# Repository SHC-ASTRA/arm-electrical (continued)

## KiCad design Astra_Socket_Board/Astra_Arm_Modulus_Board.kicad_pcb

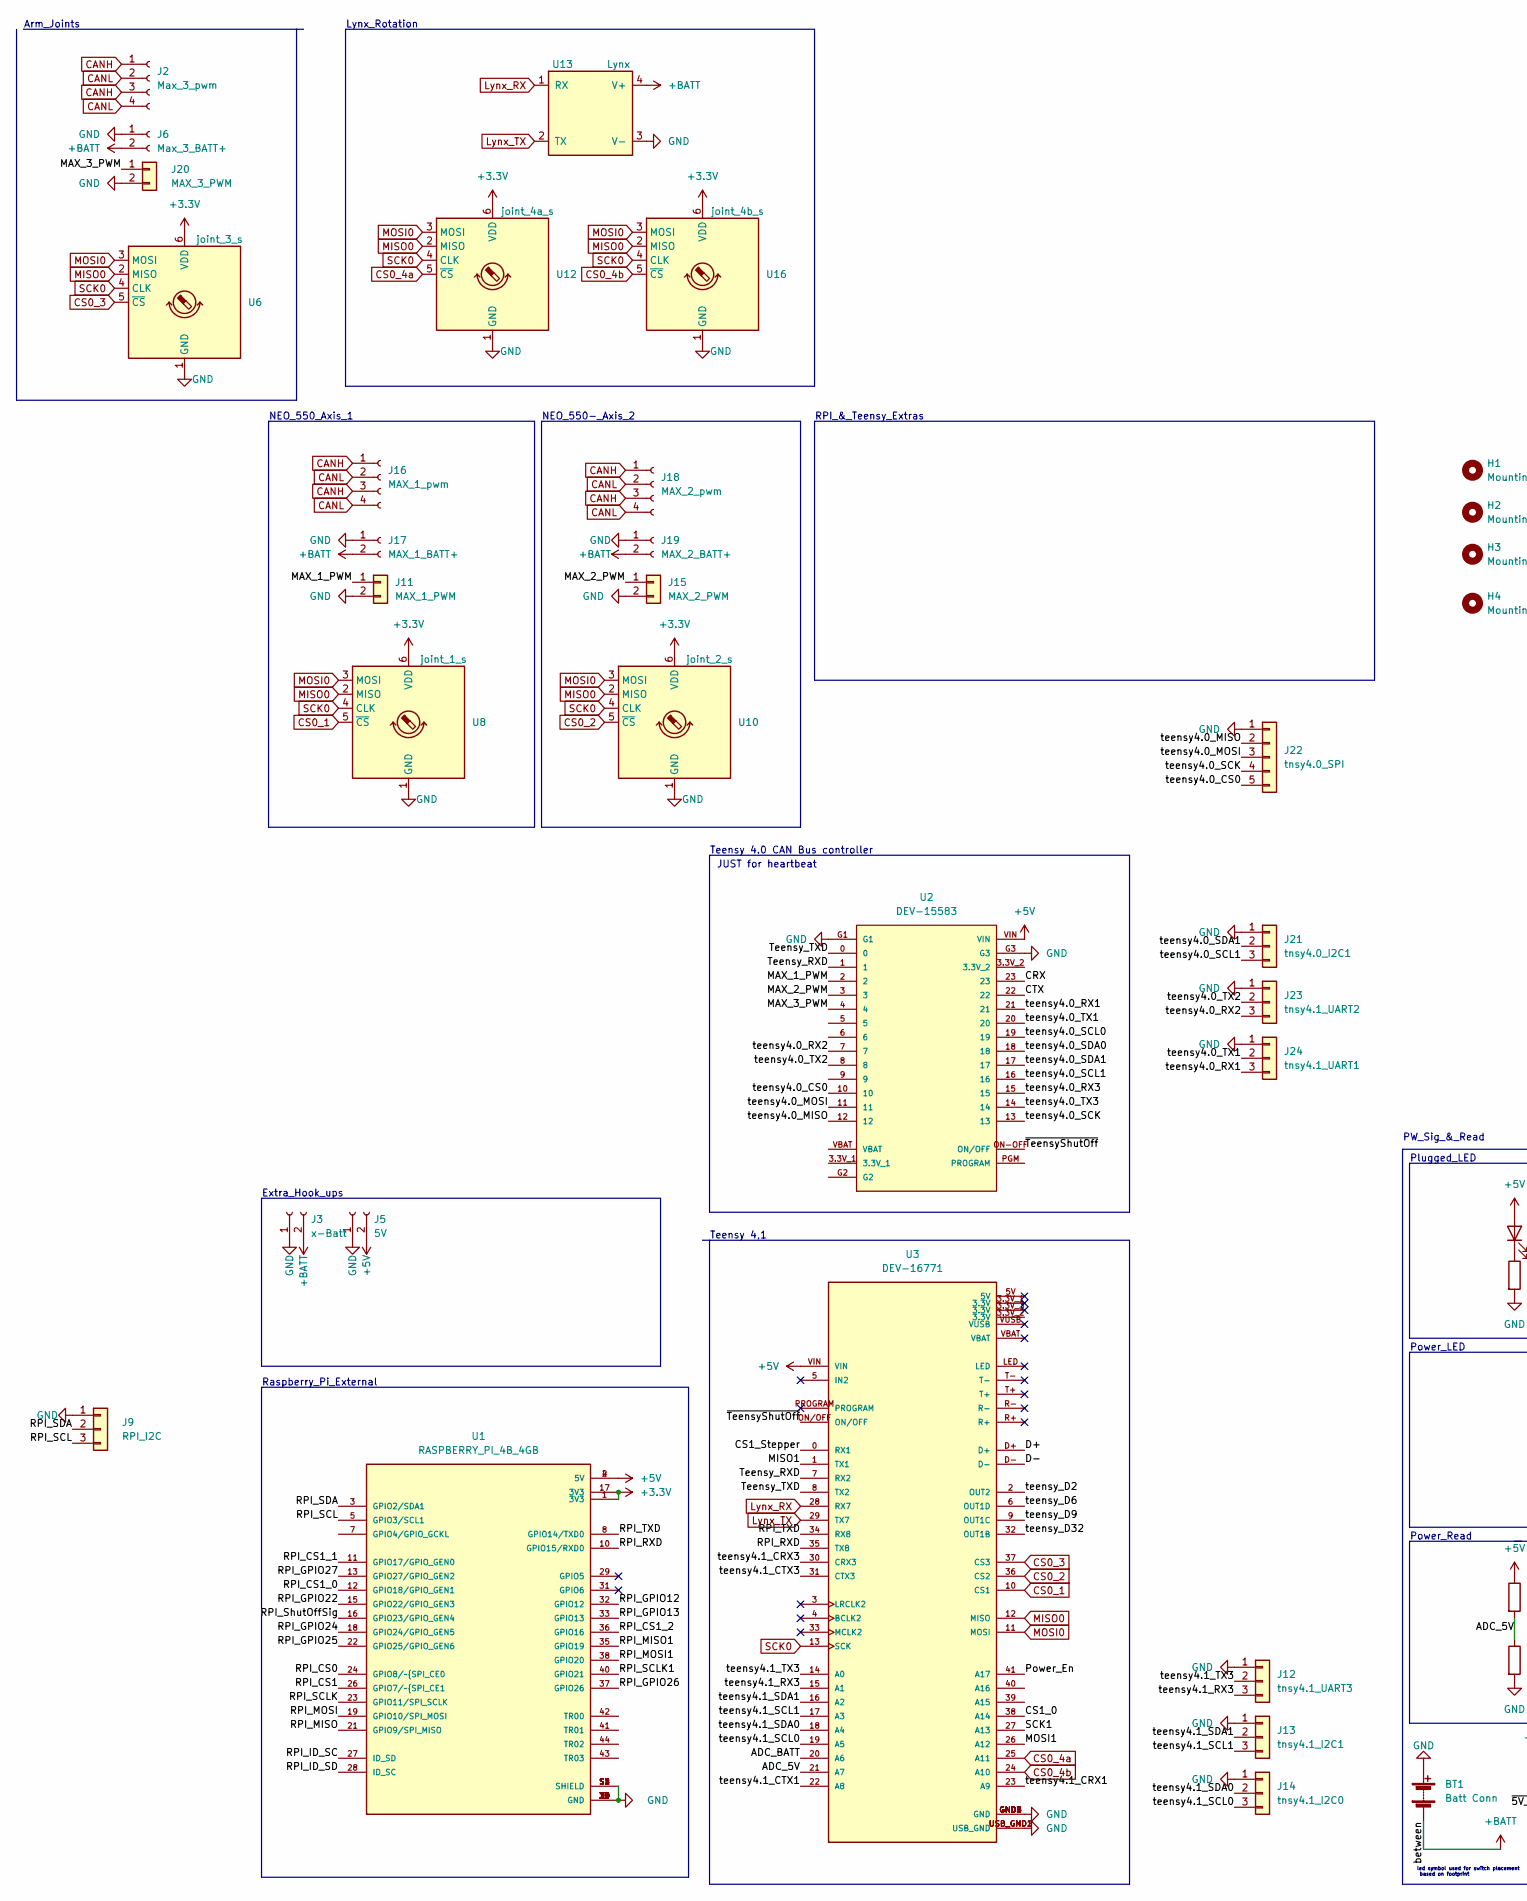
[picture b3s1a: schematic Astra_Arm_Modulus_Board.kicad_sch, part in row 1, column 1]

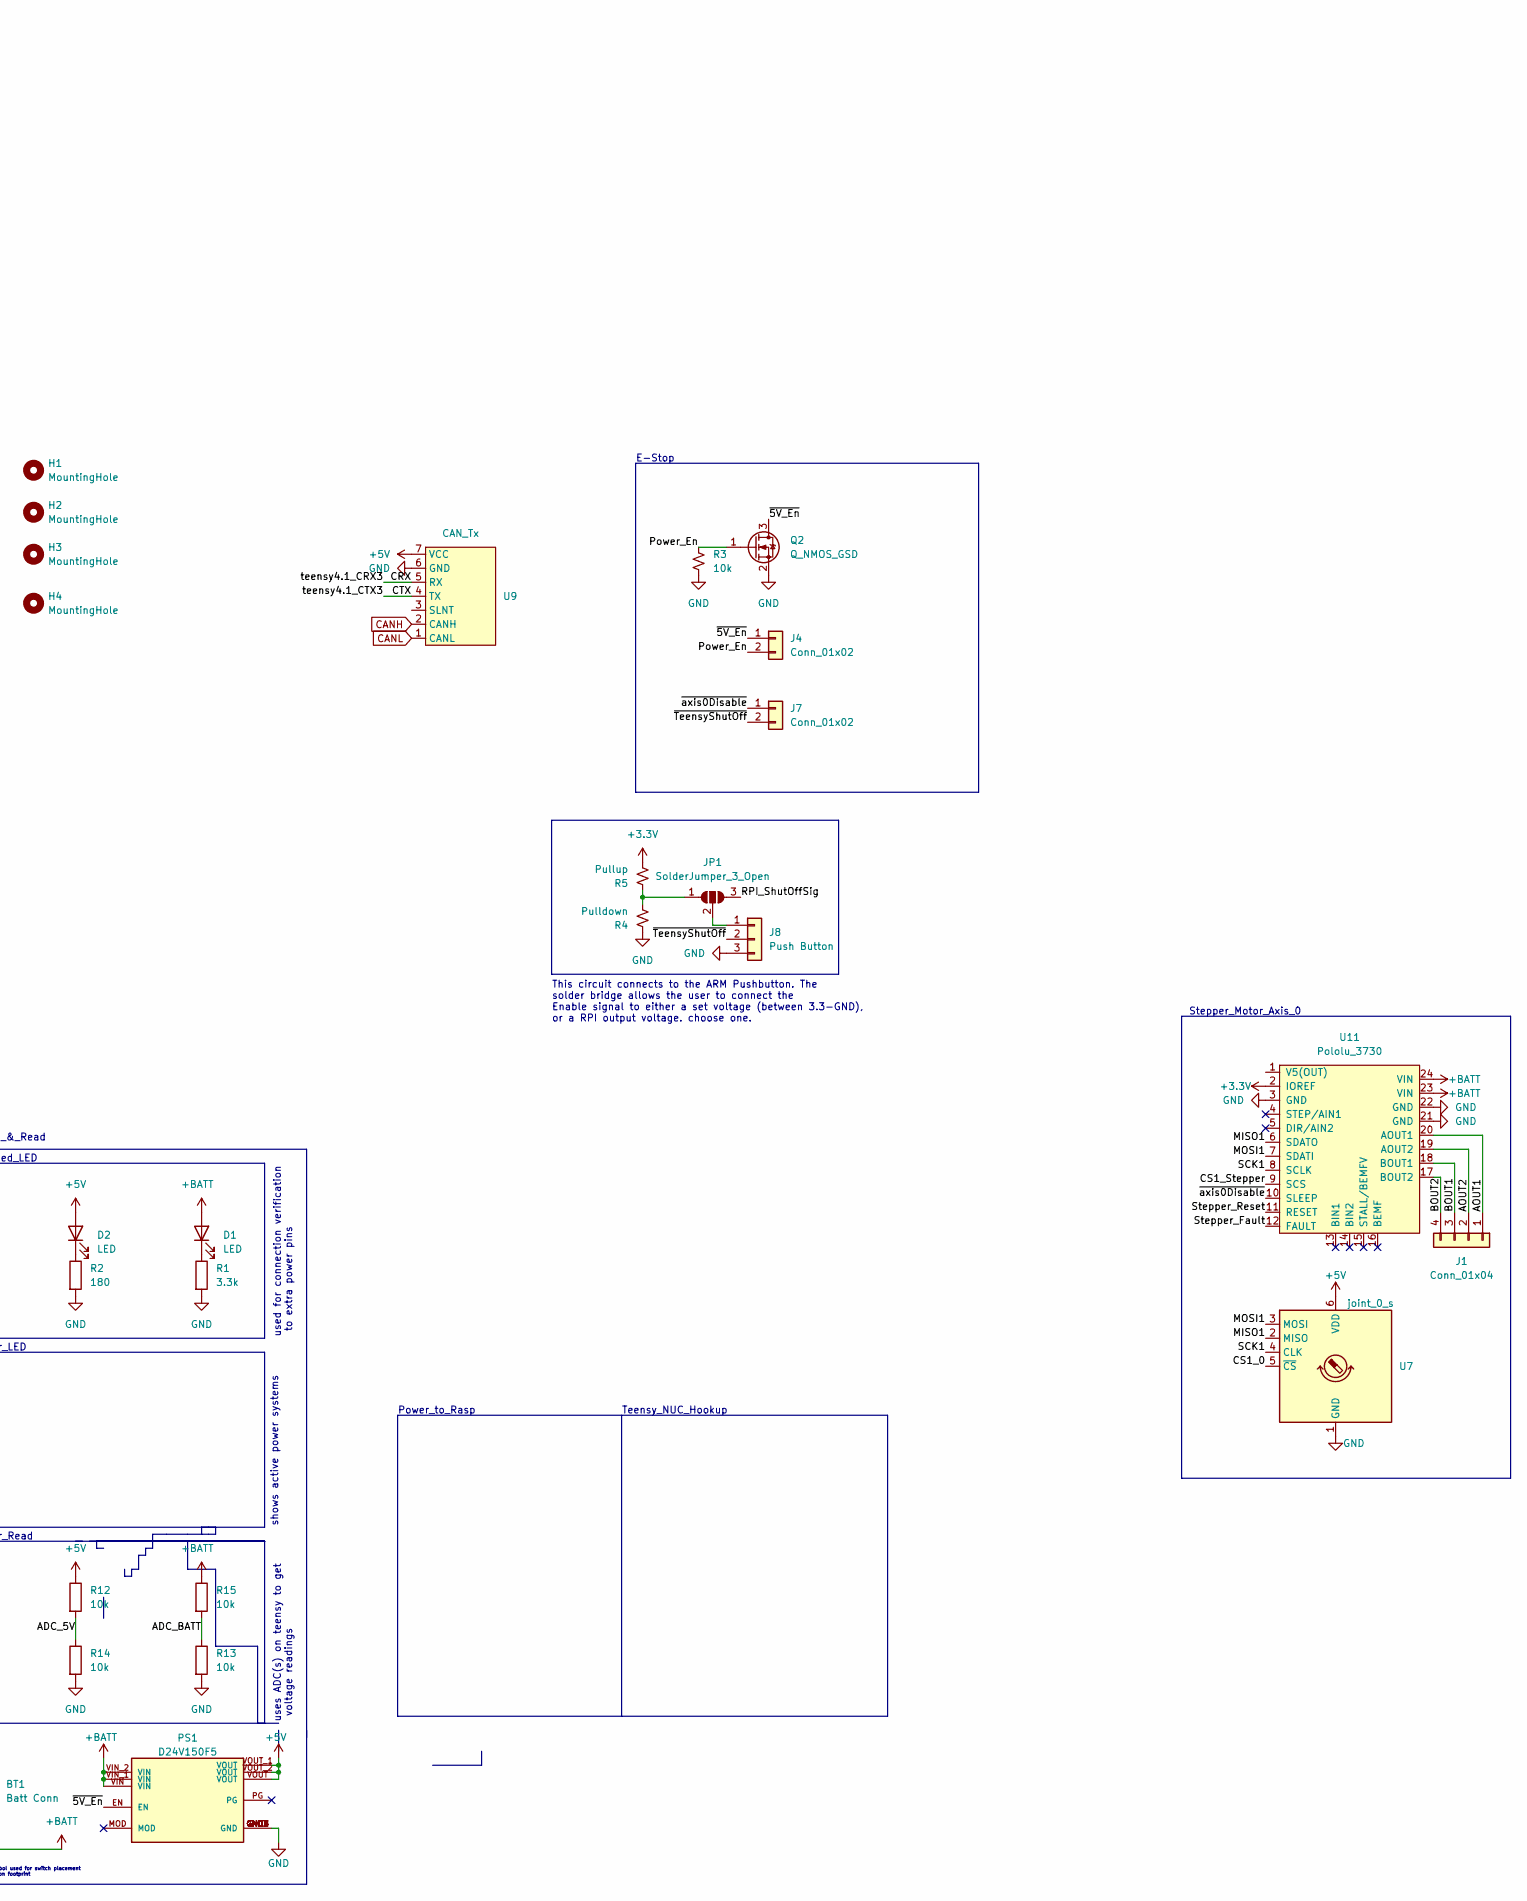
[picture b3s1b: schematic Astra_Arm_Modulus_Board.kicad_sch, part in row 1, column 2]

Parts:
BT1: Batt Conn; AMASS_XT60-F_1x02_P7.20mm_Vertical
D1, D2: LED; LED_0603_1608Metric_Pad1.05x0.95mm_HandSolder
H1, H2, H3, H4: MountingHole; MountingHole_3mm
J1: Conn_01x04; JST_XH_S4B-XH-A_1x04_P2.50mm_Horizontal
J2: Max_3_pwm; JST_EH_B4B-EH-A_1x04_P2.50mm_Vertical
J3: x-Batt; AMASS_XT60-F_1x02_P7.20mm_Vertical
J4, J7: Conn_01x02; PinSocket_1x02_P2.54mm_Vertical
J5: 5V; AMASS_XT60-F_1x02_P7.20mm_Vertical
J6: Max_3_BATT+; AMASS_XT60-F_1x02_P7.20mm_Vertical
J8: Push Button; JST_PH_B3B-PH-K_1x03_P2.00mm_Vertical
J9: RPI_I2C; PinHeader_1x03_P2.54mm_Vertical
J11: MAX_1_PWM; JST_PH_B2B-PH-K_1x02_P2.00mm_Vertical
J12: tnsy4.1_UART3; PinHeader_1x03_P2.54mm_Vertical
J13: tnsy4.1_I2C1; PinHeader_1x03_P2.54mm_Vertical
J14: tnsy4.1_I2C0; PinHeader_1x03_P2.54mm_Vertical
J15: MAX_2_PWM; JST_PH_B2B-PH-K_1x02_P2.00mm_Vertical
J16: MAX_1_pwm; JST_EH_B4B-EH-A_1x04_P2.50mm_Vertical
J17: MAX_1_BATT+; AMASS_XT60-F_1x02_P7.20mm_Vertical
J18: MAX_2_pwm; JST_EH_B4B-EH-A_1x04_P2.50mm_Vertical
J19: MAX_2_BATT+; AMASS_XT60-F_1x02_P7.20mm_Vertical
J20: MAX_3_PWM; JST_PH_B2B-PH-K_1x02_P2.00mm_Vertical
J21: tnsy4.0_I2C1; PinHeader_1x03_P2.54mm_Vertical
J22: tnsy4.0_SPI; PinHeader_1x05_P2.54mm_Vertical
J23: tnsy4.1_UART2; PinHeader_1x03_P2.54mm_Vertical
J24: tnsy4.1_UART1; PinHeader_1x03_P2.54mm_Vertical
JP1: SolderJumper_3_Open; SolderJumper-3_P1.3mm_Open_RoundedPad1.0x1.5mm
PS1: D24V150F5; POLOLU_D24V150F5; PARTREV 27/09/2016
Q2: Q_NMOS_GSD; SOT-23
R1: 3.3k; R_0603_1608Metric_Pad0.98x0.95mm_HandSolder
R2: 180; R_0603_1608Metric_Pad0.98x0.95mm_HandSolder
R3, R12, R13, R14, R15: 10k; R_0603_1608Metric_Pad0.98x0.95mm_HandSolder
R4: Pulldown; R_0603_1608Metric_Pad0.98x0.95mm_HandSolder
R5: Pullup; R_0603_1608Metric_Pad0.98x0.95mm_HandSolder
U1: RASPBERRY_PI_4B_4GB; MODULE_RASPBERRY_PI_4B_4GB; PARTREV 4
U2: DEV-15583; MODULE_DEV-15583
U3: DEV-16771; MODULE_DEV-16771; PARTREV 4.1
U6: joint_3_s; JST_EH_B6B-EH-A_1x06_P2.50mm_Vertical
U7: joint_0_s; JST_EH_S6B-EH_1x06_P2.50mm_Horizontal
U8: joint_1_s; JST_EH_B6B-EH-A_1x06_P2.50mm_Vertical
U9: CAN_Tx; Adafruit_CAN_Pal
U10: joint_2_s; JST_EH_B6B-EH-A_1x06_P2.50mm_Vertical
U11: Pololu_3730
U12: joint_4a_s; JST_EH_B6B-EH-A_1x06_P2.50mm_Vertical
U13: Lynx; JST_EH_B4B-EH-A_1x04_P2.50mm_Vertical
U16: joint_4b_s; JST_EH_B6B-EH-A_1x06_P2.50mm_Vertical

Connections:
+3.3V: R5.2, U1.1 (3V3), U1.17 (3V3), U6.6 (VDD), U8.6 (VDD), U10.6 (VDD), U11.2 (IOREF), U12.6 (VDD), U16.6 (VDD)
+5V: D2.2 (A), J5.2, PS1.VOUT, PS1.VOUT_1 (VOUT), PS1.VOUT_2 (VOUT), R12.1, U1.2 (5V), U1.4 (5V), U2.VIN, U3.VIN, U7.6 (VDD), U9.7 (VCC)
+BATT: BT1.2 (-), D1.2 (A), J3.2, J6.2, J17.2, J19.2, PS1.VIN, PS1.VIN_1 (VIN), PS1.VIN_2 (VIN), R15.1, U11.23 (VIN), U11.24 (VIN), U13.4 (V+)
/ADC_5V: R12.2, R14.1, U3.21 (A7)
/ADC_BATT: R13.1, R15.2, U3.20 (A6)
/AOUT1: J1.1, U11.20 (AOUT1)
/AOUT2: J1.2, U11.19 (AOUT2)
/BOUT1: J1.3, U11.18 (BOUT1)
/BOUT2: J1.4, U11.17 (BOUT2)
/CRX: U2.23, U3.30 (CRX3), U9.5 (RX)
/CS1_0: U3.38 (A14), U7.5 (~CS)
/CS1_Stepper: U3.0 (RX1), U11.9 (SCS)
/CTX: U2.22, U3.31 (CTX3), U9.4 (TX)
/MAX_1_PWM: J11.1, U2.2
/MAX_2_PWM: J15.1, U2.3
/MAX_3_PWM: J20.1, U2.4
/MISO1: U3.1 (TX1), U7.2 (MISO), U11.6 (SDATO)
/MOSI1: U3.26 (A12), U7.3 (MOSI), U11.7 (SDATI)
/Power_En: J4.2, Q2.1 (G), R3.2, U3.41 (A17)
/RPI_CS0: U1.24 (GPIO8/~SPI_CE0~{)
/RPI_CS1: U1.26 (GPIO7/~SPI_CE1~{)
/RPI_CS1_0: U1.12 (GPIO18/GPIO_GEN1)
/RPI_CS1_1: U1.11 (GPIO17/GPIO_GEN0)
/RPI_CS1_2: U1.36 (GPIO16)
/RPI_GPIO12: U1.32 (GPIO12)
/RPI_GPIO13: U1.33 (GPIO13)
/RPI_GPIO22: U1.15 (GPIO22/GPIO_GEN3)
/RPI_GPIO24: U1.18 (GPIO24/GPIO_GEN5)
/RPI_GPIO25: U1.22 (GPIO25/GPIO_GEN6)
/RPI_GPIO26: U1.37 (GPIO26)
/RPI_GPIO27: U1.13 (GPIO27/GPIO_GEN2)
/RPI_ID_SC: U1.27 (ID_SD)
/RPI_ID_SD: U1.28 (ID_SC)
/RPI_MISO: U1.21 (GPIO9/SPI_MISO)
/RPI_MISO1: U1.35 (GPIO19)
/RPI_MOSI: U1.19 (GPIO10/SPI_MOSI)
/RPI_MOSI1: U1.38 (GPIO20)
/RPI_RXD: U1.10 (GPIO15/RXD0), U3.35 (TX8)
/RPI_SCL: J9.3, U1.5 (GPIO3/SCL1)
/RPI_SCLK: U1.23 (GPIO11/SPI_SCLK)
/RPI_SCLK1: U1.40 (GPIO21)
/RPI_SDA: J9.2, U1.3 (GPIO2/SDA1)
/RPI_ShutOffSig: JP1.3 (B), U1.16 (GPIO23/GPIO_GEN4)
/RPI_TXD: U1.8 (GPIO14/TXD0), U3.34 (RX8)
/SCK1: U3.27 (A13), U7.4 (CLK), U11.8 (SCLK)
/Stepper_Fault: U11.12 (FAULT)
/Stepper_Reset: U11.11 (RESET)
/Teensy_RXD: U2.1, U3.7 (RX2)
/Teensy_TXD: U2.0, U3.8 (TX2)
/teensy4.0_CS0: J22.5, U2.10
/teensy4.0_MISO: J22.2, U2.12
/teensy4.0_MOSI: J22.3, U2.11
/teensy4.0_RX1: J24.3, U2.21
/teensy4.0_RX2: J23.3, U2.7
/teensy4.0_RX3: U2.15
/teensy4.0_SCK: J22.4, U2.13
/teensy4.0_SCL0: U2.19
/teensy4.0_SCL1: J21.3, U2.16
/teensy4.0_SDA0: U2.18
/teensy4.0_SDA1: J21.2, U2.17
/teensy4.0_TX1: J24.2, U2.20
/teensy4.0_TX2: J23.2, U2.8
/teensy4.0_TX3: U2.14
/teensy4.1_CRX1: U3.23 (A9)
/teensy4.1_CTX1: U3.22 (A8)
/teensy4.1_RX3: J12.3, U3.15 (A1)
/teensy4.1_SCL0: J14.3, U3.19 (A5)
/teensy4.1_SCL1: J13.3, U3.17 (A3)
/teensy4.1_SDA0: J14.2, U3.18 (A4)
/teensy4.1_SDA1: J13.2, U3.16 (A2)
/teensy4.1_TX3: J12.2, U3.14 (A0)
/teensy_D2: U3.2 (OUT2)
/teensy_D6: U3.6 (OUT1D)
/teensy_D9: U3.9 (OUT1C)
/teensy_D32: U3.32 (OUT1B)
/~5V_En: J4.1, PS1.EN, Q2.3 (D)
/~TeensyShutOff: J7.2, J8.2, U2.ON-OFF (ON/OFF), U3.ON/OFF
/~axis0Disable: J7.1, U11.10 (SLEEP)
CANH: J2.1, J2.3, J16.1, J16.3, J18.1, J18.3, U9.2 (CANH)
CANL: J2.2, J2.4, J16.2, J16.4, J18.2, J18.4, U9.1 (CANL)
CS0_1: U3.10 (CS1), U8.5 (~CS)
CS0_2: U3.36 (CS2), U10.5 (~CS)
CS0_3: U3.37 (CS3), U6.5 (~CS)
CS0_4a: U3.25 (A11), U12.5 (~CS)
CS0_4b: U3.24 (A10), U16.5 (~CS)
GND: BT1.1 (+), J3.1, J5.1, J6.1, J8.3, J9.1, J11.2, J12.1, J13.1, J14.1, J15.2, J17.1, J19.1, J20.2, J21.1, J22.1, J23.1, J24.1, PS1.GND, PS1.GND1 (GND), PS1.GND2 (GND), PS1.GND3 (GND), PS1.GND4 (GND), PS1.GND5 (GND), PS1.GND6 (GND), PS1.GND7 (GND), Q2.2 (S), R1.2, R2.2, R3.1, R4.1, R13.2, R14.2, U1.6 (GND), U1.9 (GND), U1.14 (GND), U1.20 (GND), U1.25 (GND), U1.30 (GND), U1.34 (GND), U1.39 (GND), U1.S1 (SHIELD), U1.S2 (SHIELD), U1.S3 (SHIELD), U1.S4 (SHIELD), U2.G1, U2.G3, U3.GND1 (GND), U3.GND2 (GND), U3.GND3 (GND), U3.GND4 (GND), U3.GND5 (GND), U3.USB_GND1 (USB_GND), U3.USB_GND2 (USB_GND), U6.1 (GND), U7.1 (GND), U8.1 (GND), U9.6 (GND), U10.1 (GND), U11.3 (GND), U11.21 (GND), U11.22 (GND), U12.1 (GND), U13.3 (V-), U16.1 (GND)
Lynx_RX: U3.28 (RX7), U13.1 (RX)
Lynx_TX: U3.29 (TX7), U13.2 (TX)
MISO0: U3.12 (MISO), U6.2 (MISO), U8.2 (MISO), U10.2 (MISO), U12.2 (MISO), U16.2 (MISO)
MOSI0: U3.11 (MOSI), U6.3 (MOSI), U8.3 (MOSI), U10.3 (MOSI), U12.3 (MOSI), U16.3 (MOSI)
unnamed: D1.1 (K), R1.1
unnamed: D2.1 (K), R2.1
unnamed: J8.1, JP1.2 (C)
unnamed: JP1.1 (A), R4.2, R5.1
SCK0: U3.13 (SCK), U6.4 (CLK), U8.4 (CLK), U10.4 (CLK), U12.4 (CLK), U16.4 (CLK)

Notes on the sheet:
NEO_550_Axis_1
uses ADC(s) on teensy to get voltage readings
Raspberry_Pi_External
Teensy_NUC_Hookup
used for connection verification to extra power pins
Power_Read
This circuit connects to the ARM Pushbutton. The solder bridge allows the user to connect the Enable signal to either a set voltage (between 3.3-GND), or a RPI output voltage. choose one.
Power_to_Rasp
Power_LED
JUST for heartbeat
Extra_Hook_ups
Teensy 4.0 CAN Bus controller
NEO_550-_Axis_2
RPI_&_Teensy_Extras
Lynx_Rotation
Stepper_Motor_Axis_0
PW_Sig_&_Read
Plugged_LED
Arm_Joints
E-Stop
Teensy 4,1
shows active power systems
led symbol used for switch placement based on footprint

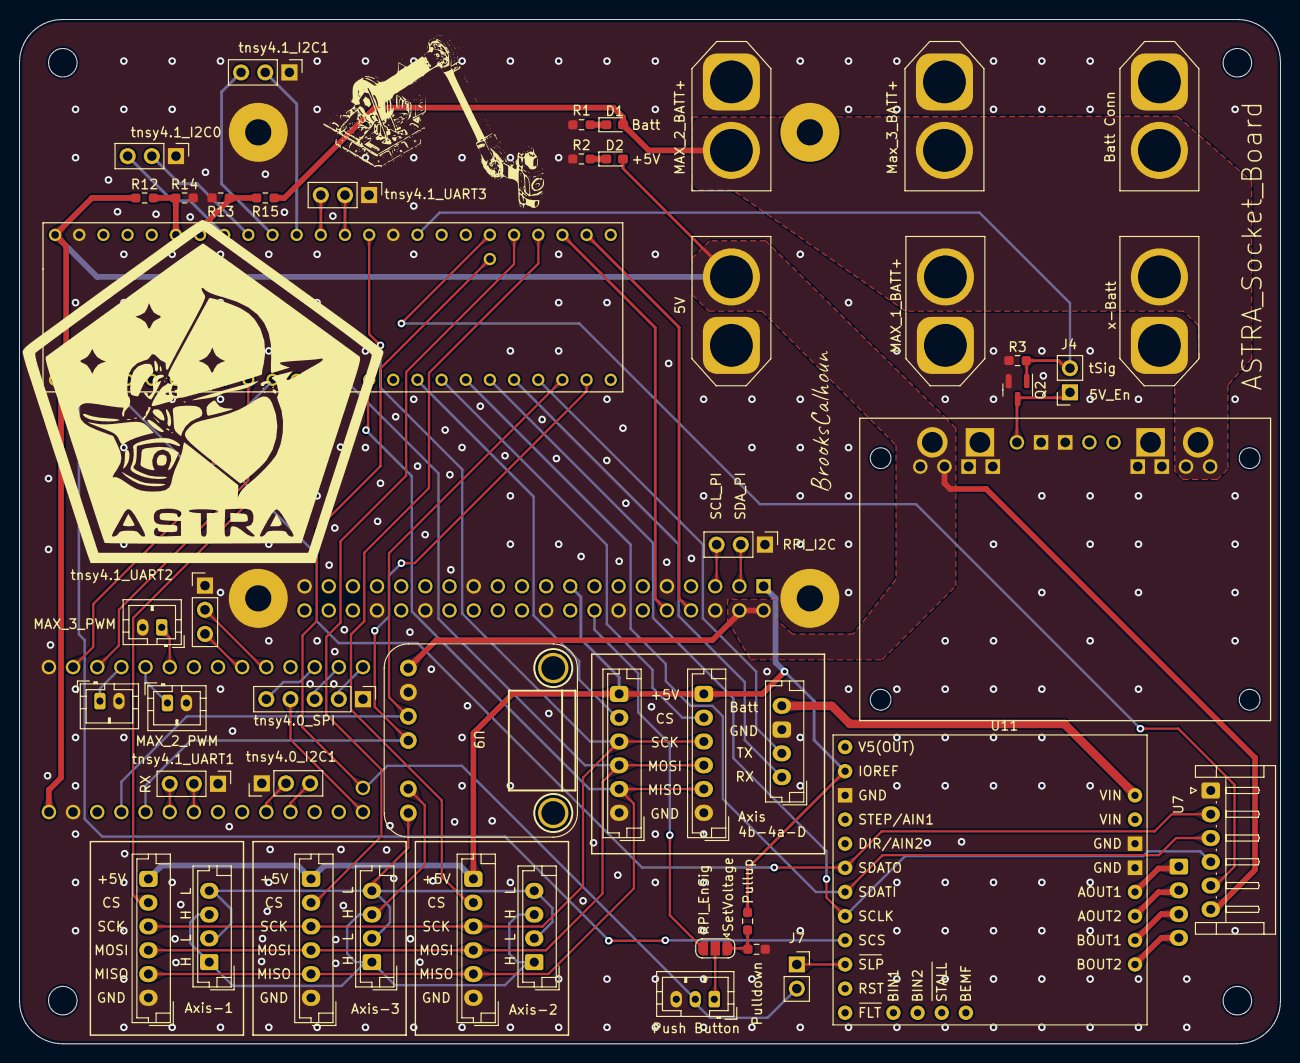
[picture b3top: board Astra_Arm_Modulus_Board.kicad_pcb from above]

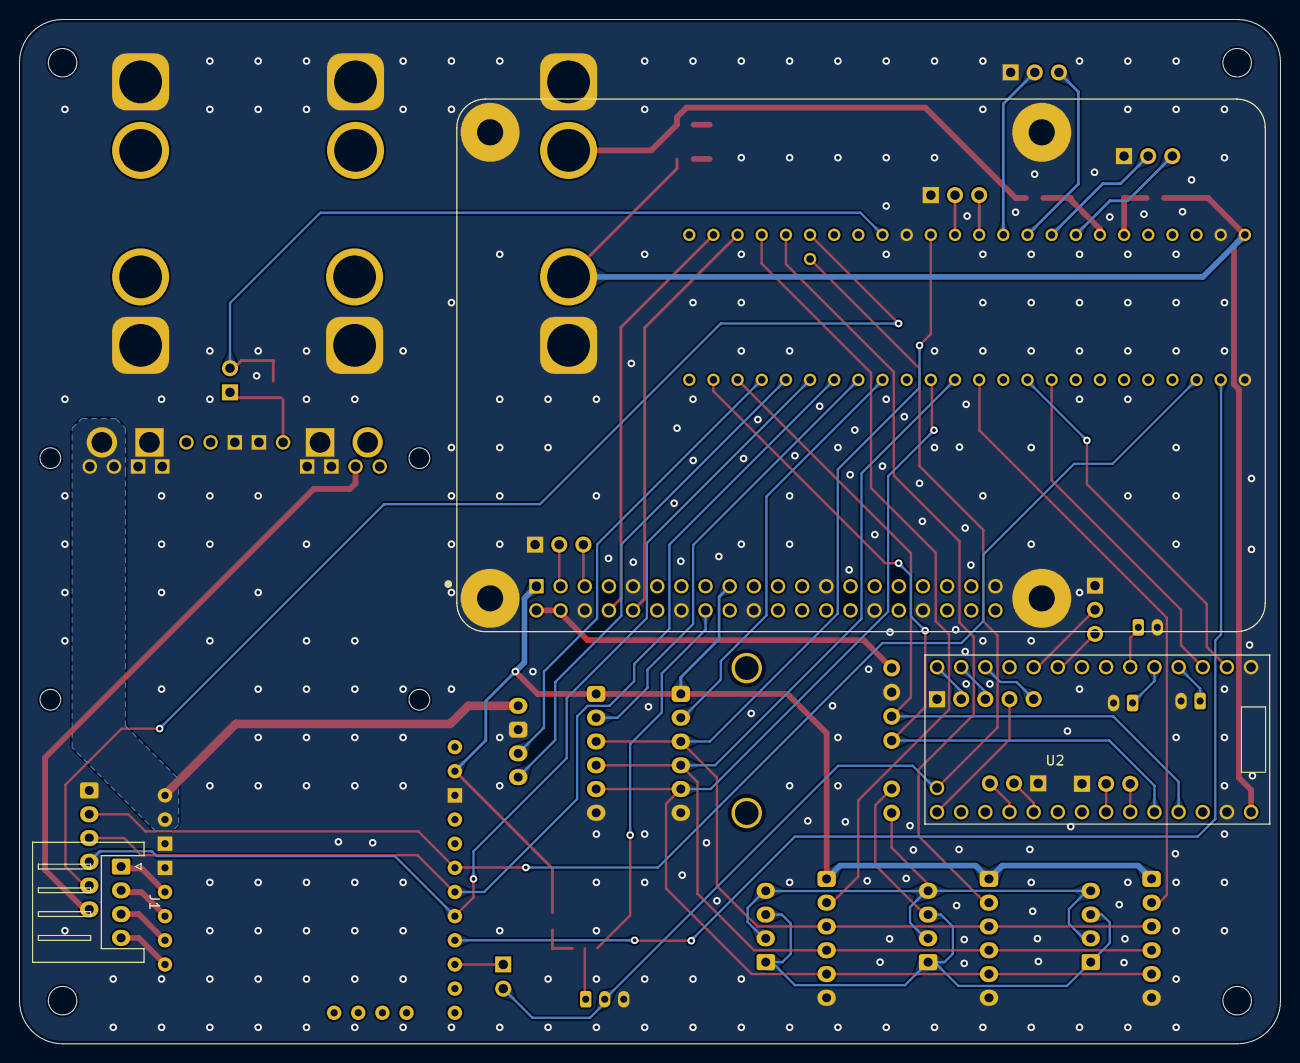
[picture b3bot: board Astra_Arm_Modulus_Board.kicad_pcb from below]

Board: 4 copper layers, 132.6 x 107.7 mm, 54 parts (2 on the bottom side), 63 nets.

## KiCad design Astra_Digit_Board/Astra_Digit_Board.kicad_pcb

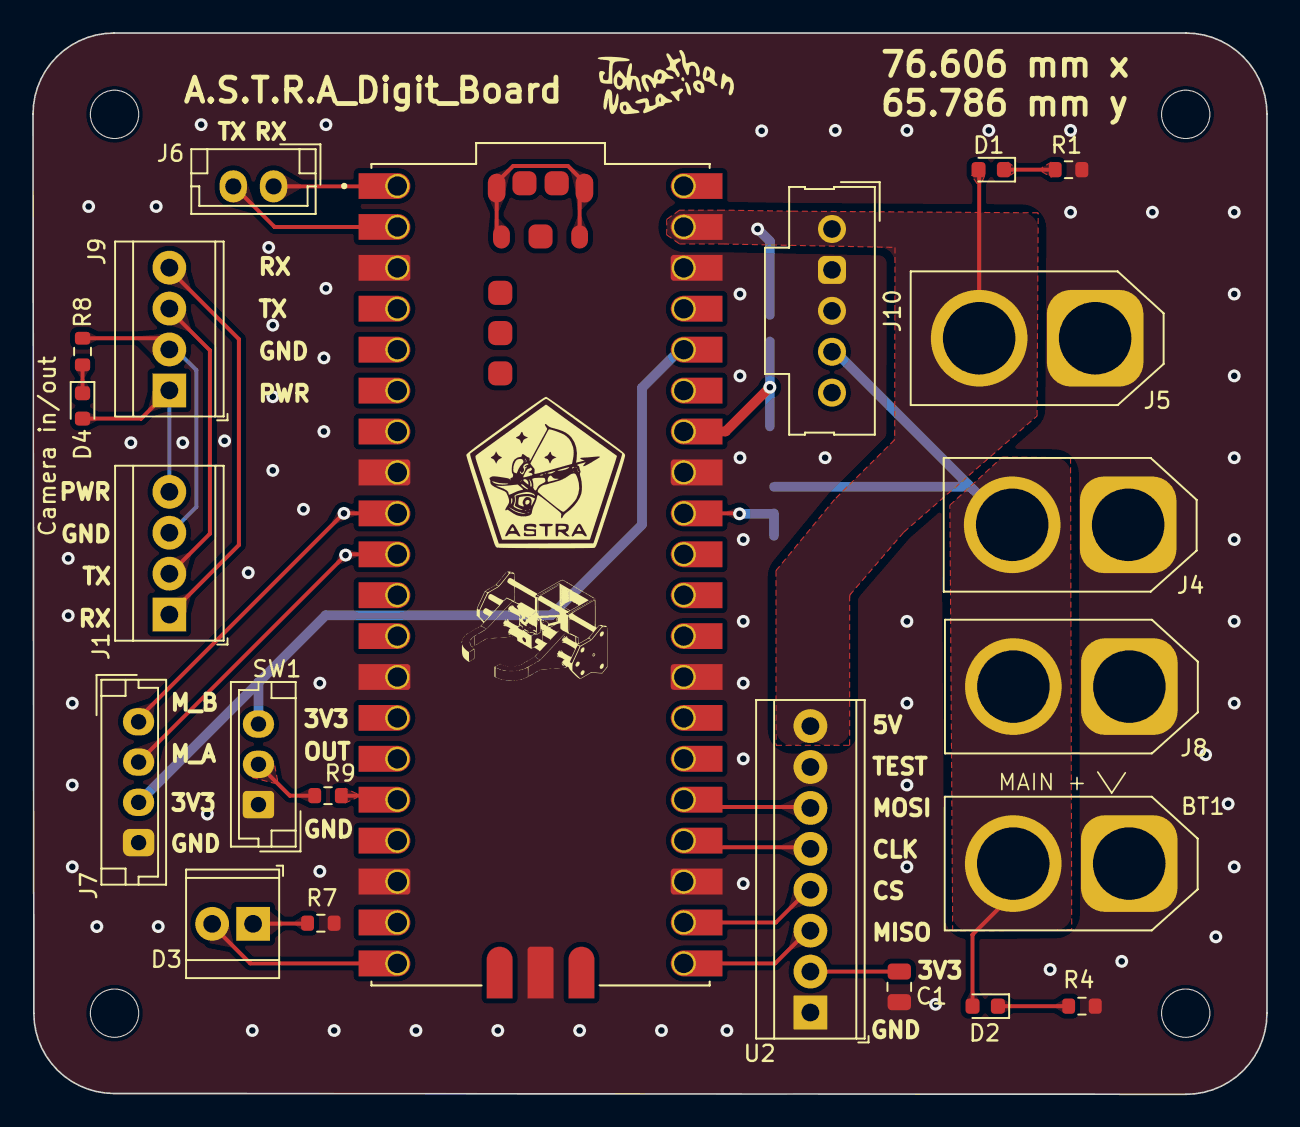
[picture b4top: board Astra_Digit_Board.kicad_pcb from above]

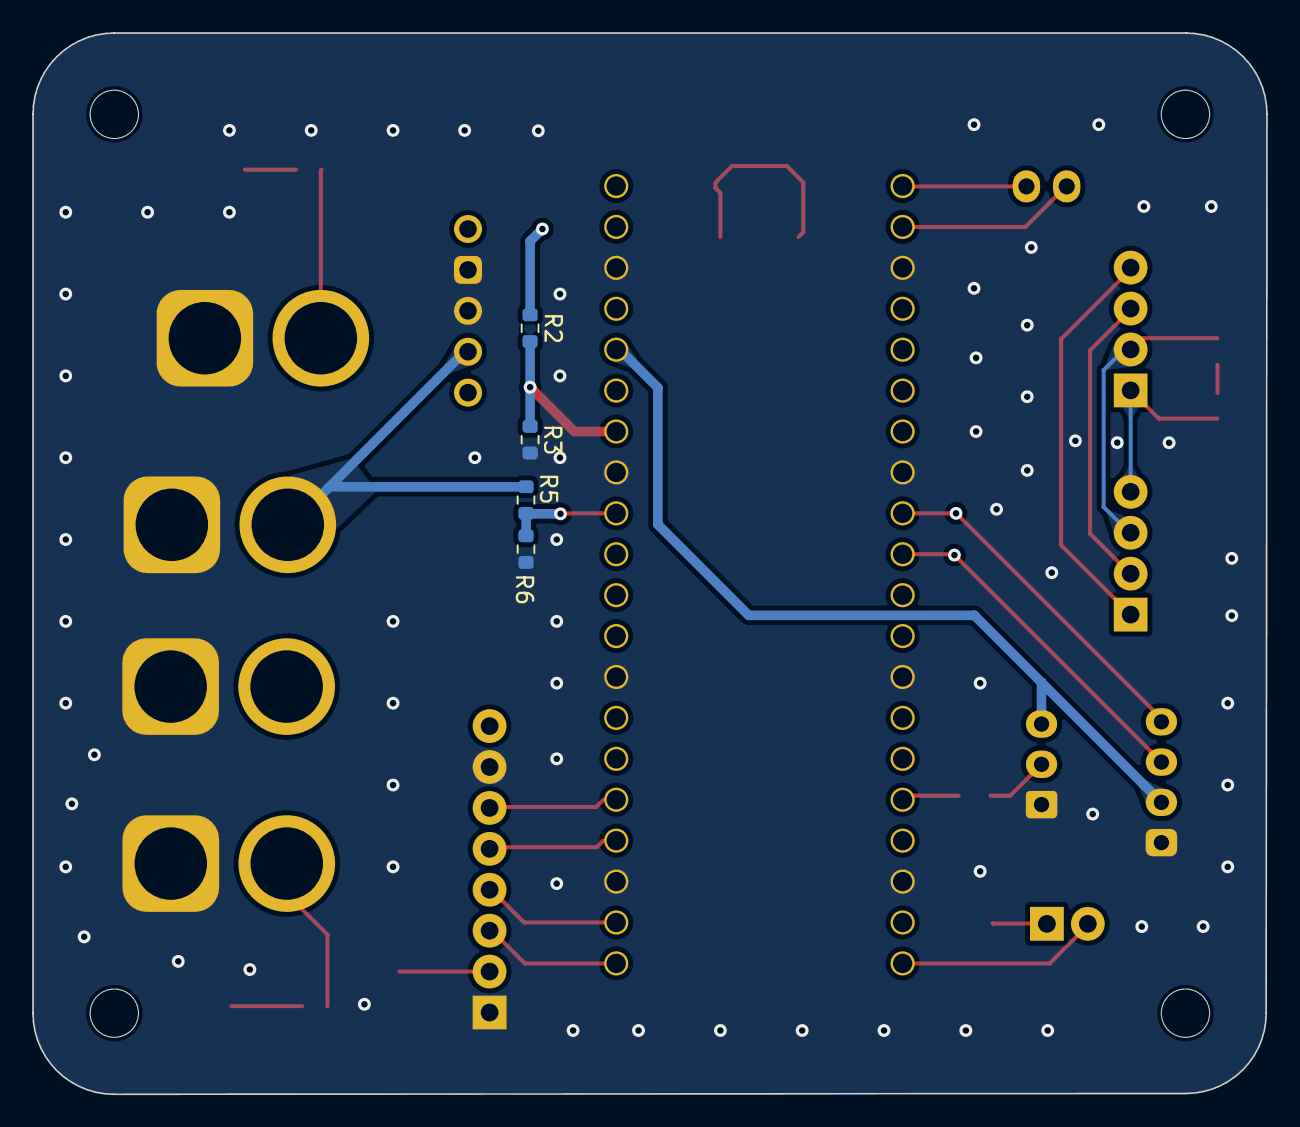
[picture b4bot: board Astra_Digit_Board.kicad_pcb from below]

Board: 2 copper layers, 76.6 x 65.9 mm, 30 parts (4 on the bottom side), 26 nets.

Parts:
BT1: Battery Connector; AMASS_XT60-F_1x02_P7.20mm_Vertical
C1: 1uF; C_0805_2012Metric
D1, D2, D4: LED; LED_0603_1608Metric
D3: GuidanceLaser; TerminalBlock_TE_282834-2_1x02_P2.54mm_Horizontal
H1, H2, H3, H4: MountingHole; MountingHole_3mm
J1: Camera_Input; TerminalBlock_TE_282834-4_1x04_P2.54mm_Horizontal
J4: Batt; AMASS_XT60-F_1x02_P7.20mm_Vertical
J5: 5V; AMASS_XT60-F_1x02_P7.20mm_Vertical
J6: Slave_UART; JST_EH_B2B-EH-A_1x02_P2.50mm_Vertical
J7: Core_Hex_sig; JST_EH_B4B-EH-A_1x04_P2.50mm_Vertical
J8: Core_Hex_PW; AMASS_XT60-F_1x02_P7.20mm_Vertical
J9: Camera_Output; TerminalBlock_TE_282834-4_1x04_P2.54mm_Horizontal
J10: D24V22F5; Molex_SL_171971-0005_1x05_P2.54mm_Vertical
R1, R8: 180; R_0603_1608Metric
R2, R3, R5, R6: 10k; R_0603_1608Metric
R4: 3.3k; R_0603_1608Metric
R7: 400; R_0603_1608Metric
R9: 6k; R_0603_1608Metric
SW1: LimitSwitch; JST_EH_B3B-EH-A_1x03_P2.50mm_Vertical
U1: SC0915; MODULE_SC0915
U2: Mandible; TerminalBlock_TE_282834-8_1x08_P2.54mm_Horizontal

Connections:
+3.3V: J7.3, SW1.3, U1.36 (3V3_OUT)
+5V: D1.2 (A), J5.2, J10.1, R2.1, U1.39 (VSYS), U2.8 (VDD)
+BATT: BT1.2 (-), D2.2 (A), J4.2, J8.2, J10.4, R5.1
/ADC_5V: R2.2, R3.1, U1.34 (GP28)
/ADC_BATT: R5.2, R6.1, U1.32 (GP27)
/Laser_GPIO15: D3.2 (A), U1.20 (GP15)
/Mandible_CLK: U1.24 (GP18), U2.5 (CLK)
/Mandible_CS: U1.22 (GP17), U2.4 (~CS)
/Mandible_MISO: U1.21 (GP16), U2.3 (MISO)
/Mandible_MOSI: U1.25 (GP19), U2.6 (MOSI)
/Mandible_chA: J7.2, U1.10 (GP7)
/Mandible_chB: J7.1, U1.9 (GP6)
/Serial_GND: J1.3, J9.2, R8.1
/Serial_PWR: D4.2 (A), J1.4, J9.1
/Serial_RX: J1.1, J9.4
/Serial_TX: J1.2, J9.3
/Slave_RXD: J6.1, U1.1 (GP0)
/Slave_TXD: J6.2, U1.2 (GP1)
/Switch_Signal: R9.2, SW1.2
GND: BT1.1 (+), C1.1, J4.1, J5.1, J7.4, J8.1, J10.2, J10.3, R1.2, R3.2, R4.2, R6.2, R7.2, SW1.1 (GND), U1.3 (GND), U1.8 (GND), U1.13 (GND), U1.18 (GND), U1.23 (GND), U1.28 (GND), U1.33 (AGND), U1.38 (GND), U1.D2 (GND), U2.1 (GND), U2.7 (TST)
unnamed: D1.1 (K), R1.1
unnamed: D2.1 (K), R4.1
unnamed: D3.1 (K), R7.1
unnamed: D4.1 (K), R8.2
unnamed: R9.1, U1.16 (GP12)
unnamed: C1.2, U2.2 (VDD3V3)

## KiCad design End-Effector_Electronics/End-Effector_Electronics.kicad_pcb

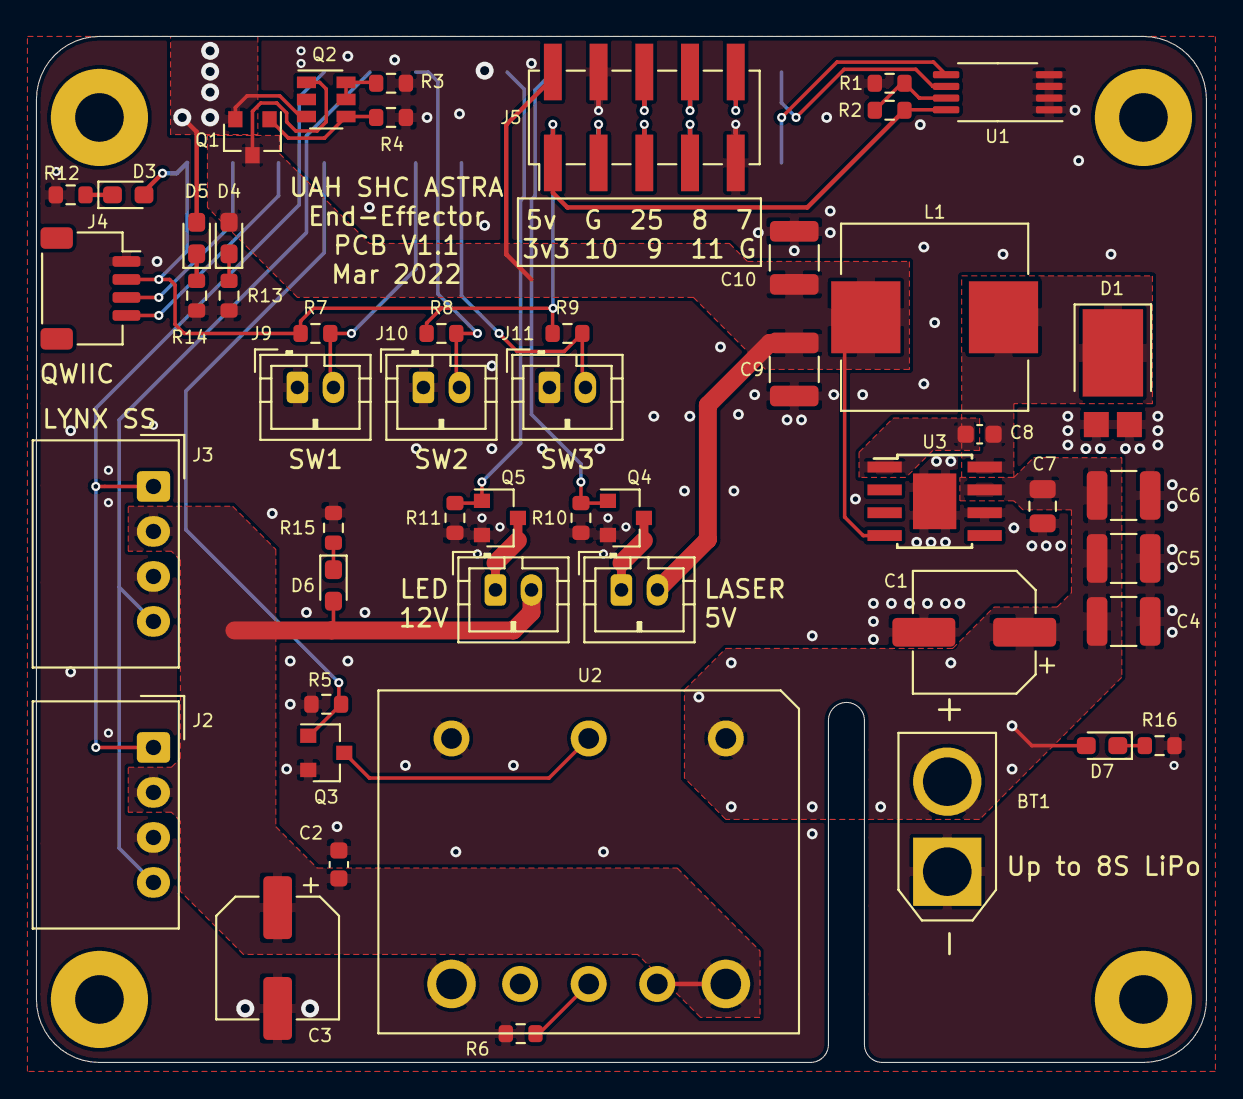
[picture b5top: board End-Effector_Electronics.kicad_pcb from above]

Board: 2 copper layers, 65.0 x 57.0 mm, 56 parts (1 on the bottom side), 38 nets.

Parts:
BT1: XT_Battery_Connector; AMASS_XT30U-M_1x02_P5.0mm_Vertical
C1: 33u; CP_Elec_6.3x5.4
C2: 0.1u; C_0603_1608Metric
C3: 22uF; CP_Elec_6.3x5.4
C4, C5, C6: 10u; C_1210_3225Metric
C7: 1u; C_0805_2012Metric
C8: 10n; C_0603_1608Metric
C9, C10: 47u; C_1210_3225Metric
D1: D_Schottky; D_PowerDI-5
D2: LED; JST_PH_B2B-PH-K_1x02_P2.00mm_Vertical
D3, D4, D5, D6, D7: G; LED_0603_1608Metric_Pad1.05x0.95mm_HandSolder
H1, H2, H3, H4: MountingHole_Pad; MountingHole_2.7mm_M2.5_Pad
J1: Raspberry_Pi_2_3; PinSocket_2x20_P2.54mm_Vertical_SMD
J2, J3: LynxServo; Molex_SPOX_5268-04A_1x04_P2.50mm_Horizontal
J4: QWIIC_Generic_Conn; JST_SH_SM04B-SRSS-TB_1x04-1MP_P1.00mm_Horizontal
J5: Conn_02x05_Odd_Even; PinHeader_2x05_P2.54mm_Vertical_SMD
J9, J10, J11: SW_Push_Open; JST_PH_B2B-PH-K_1x02_P2.00mm_Vertical
L1: 18u; L_Wuerth_HCI-1050
LD1: Laserdiode_1C2A; JST_PH_B2B-PH-K_1x02_P2.00mm_Vertical
Q1: Q_PMOS_GSD; SOT-23
Q2: DMMT3906; SOT-23-6
Q3, Q4, Q5: Q_NMOS_GSD; SOT-23
R1: DNP; R_0603_1608Metric
R2, R3: 10k; R_0603_1608Metric
R4: 47k; R_0603_1608Metric
R5, R7, R8, R9, R10, R11: 100k; R_0603_1608Metric
R6: 1.82k; R_0603_1608Metric
R12: 10; R_0603_1608Metric
R13, R14: 180; R_0603_1608Metric
R15: 1k; R_0603_1608Metric
R16: 3.3k; R_0603_1608Metric
U1: CAT24C32; TSSOP-8_4.4x3mm_P0.65mm
U2: TDK_I3A4W008A033V; Power_Supply_32nd_Brick
U3: LM22676MR-5; TI_SO-PowerPAD-8

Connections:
+3V3: D3.2, J1.1, J1.17, J4.2, J5.1, R2.2, R7.1, R8.1, R9.1, U1.8
+5V: C9.1, C10.1, D4.2, J5.2, L1.2, LD1.2, Q1.3, Q2.1, U3.4
+12V: C2.1, C3.1, D2.2, D6.2, J2.2, J3.2, U2.7, U2.8
+BATT: BT1.2, C1.1, C4.1, C5.1, C6.1, C7.1, D7.2, U2.1, U3.7
/5V_RPI: D5.2, J1.2, J1.4, Q1.2, Q2.3
/12V_Disable: J1.7, Q3.1, R5.1
/GPIO7: J1.26, J5.10
/GPIO8: J1.24, J5.8
/GPIO9: J1.21, J5.5
/GPIO10: J1.19, J5.3
/GPIO11: J1.23, J5.7
/GPIO25: J1.22, J5.6
/ID_SCL: J1.28, U1.6
/ID_SDA: J1.27, U1.5
/LED: J1.16, Q5.1, R11.1
/Laser: J1.18, Q4.1, R10.1
/Limit_SW1: J1.11, J9.2, R7.2
/Limit_SW2: J1.12, J10.2, R8.2
/Limit_SW3: J1.13, J11.2, R9.2
/SCL: J1.5, J4.4
/SDA: J1.3, J4.3
/ServoRX: J1.8, J2.1, J3.1
/ServoTX: J1.10, J2.4, J3.4
GND: BT1.1, C1.2, C2.2, C3.2, C4.2, C5.2, C6.2, C7.2, C9.2, C10.2, D1.2, J1.6, J1.9, J1.14, J1.20, J1.25, J1.30, J1.34, J1.39, J2.3, J3.3, J4.1, J5.4, J5.9, J9.1, J10.1, J11.1, Q3.2, Q4.2, Q5.2, R1.2, R3.1, R4.2, R5.2, R6.2, R10.2, R11.2, R12.2, R13.2, R14.2, R15.2, R16.2, U1.1, U1.2, U1.3, U1.4, U2.3, U2.4, U3.6, U3.9
unnamed: C8.1, U3.1
unnamed: C8.2, D1.1, L1.1, U3.8
unnamed: D2.1, Q5.3
unnamed: D3.1, R12.1
unnamed: D4.1, R13.1
unnamed: D5.1, R14.1
unnamed: D6.1, R15.1
unnamed: D7.1, R16.1
unnamed: LD1.1, Q4.3
unnamed: Q1.1, Q2.4, R4.1
unnamed: Q2.5, Q2.6, R3.2
unnamed: Q3.3, U2.2
unnamed: R1.1, R2.1, U1.7
unnamed: R6.1, U2.6

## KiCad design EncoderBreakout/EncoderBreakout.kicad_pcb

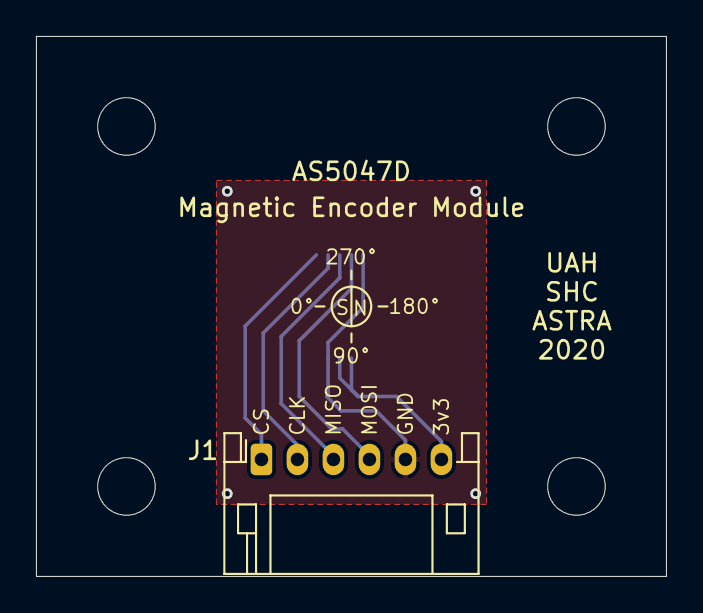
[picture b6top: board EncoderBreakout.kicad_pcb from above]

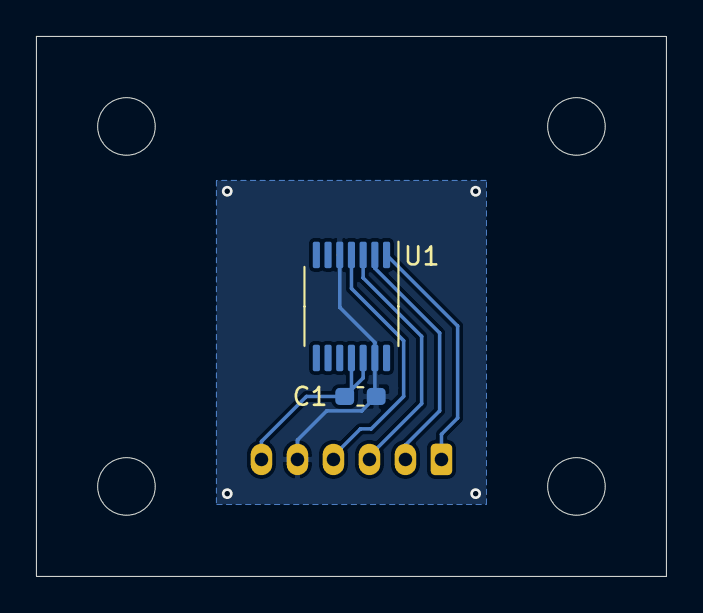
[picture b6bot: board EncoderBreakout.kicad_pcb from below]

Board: 2 copper layers, 35.0 x 30.0 mm, 7 parts (2 on the bottom side), 6 nets.

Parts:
C1: 0.1u; C_0603_1608Metric_Pad1.05x0.95mm_HandSolder
H1, H2, H3, H4: MountingHole; MountingHole_3.2mm_M3
J1: Conn_01x06; JST_PH_S6B-PH-K_1x06_P2.00mm_Horizontal
U1: AS5047D; TSSOP-14_4.4x5mm_P0.65mm

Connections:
+3V3: C1.1, J1.6, U1.11, U1.12
GND: C1.2, J1.5, U1.5, U1.13
unnamed: J1.1, U1.1
unnamed: J1.2, U1.2
unnamed: J1.3, U1.3
unnamed: J1.4, U1.4

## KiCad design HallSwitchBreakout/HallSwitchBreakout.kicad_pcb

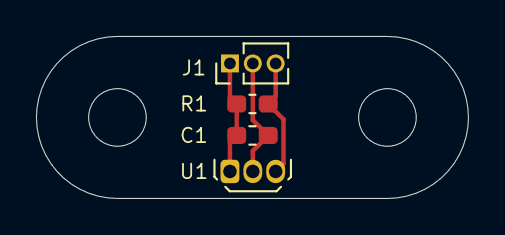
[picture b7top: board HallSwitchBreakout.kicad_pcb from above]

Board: 2 copper layers, 24.0 x 9.0 mm, 6 parts (0 on the bottom side), 3 nets.

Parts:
C1: 0.1u; C_0603_1608Metric_Pad1.05x0.95mm_HandSolder
H1, H2: MountingHole; MountingHole_3.2mm_M3
J1: Conn_01x03; PinHeader_1x03_P1.27mm_Vertical
R1: 10k; R_0603_1608Metric_Pad1.05x0.95mm_HandSolder
U1: AH1815-P-B; TO-92Flat

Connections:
/out: J1.3, R1.2, U1.3
GND: C1.2, J1.2, U1.2
VCC: C1.1, J1.1, R1.1, U1.1
